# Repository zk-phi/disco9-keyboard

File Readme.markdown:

# よく光るマクロパッド

実験要素を多く含んだ９キーのマクロパッドです

- ２軸ジョイスティック (http://akizukidenshi.com/catalog/g/gP-04048/) を取り付けられます
- バックライト LED をスイッチとスイッチの間にもつけることができ、 LED 穴のついていないスイッチでも光らせられます
- (プレートがあれば ALPS スイッチも取り付けられます)

ジョイスティックは自由に値を取得して利用することができます。デフォルトのファームウェアにはカーソルを移動するサンプルが実装されています。

## パーツ

- 基板２枚 (片方は底板として利用)
- いつもの
  - ダイオード 1N4148w x9
  - 2 ピンタクトスイッチ x1
  - コンスルー付き ProMicro x1
- LED
  - SK6812mini 最大 x21
- ジョイスティック
  - JT8P-3.2T-B10K-1-16Y x1
- スイッチ
  - MX スイッチ x9
  - (プレートを用意すれば ALPS スイッチも可)
- ネジ類
  - M2 スペーサ 5mm 4 個
  - M2 ネジ 3~4mm 8 個
  - ゴム足 4 個

## 組み立て

- ダイオードを実装します
  - コの字の目印がカソード
  - ファームウェアを焼いたコンスルー付き ProMicro を差し込み、キースイッチのピンを接続する穴をピンセットなどでショートすることで動作確認できます

- LED を実装します
  - コの字の目印が Vcc
  - 穴に落とし込んで実装する普通のバックライトを、上段から下段に向かって図の順に
  - その後、表面に実装する怪しいバックライトを、今度は下段から上段に向かって図の順に
  - 途中まで実装した状態でも動作確認できます
    - ファームウェアを焼いたコンスルー付き ProMicro を差し込む
    - もし光らなければ、 RGB_TOG キーを (ピンセットなどでショートして) 押してみます
    - それでも光らない、あるいは不自然な点滅をしているなどの場合はハンダを付け直します

- タクトスイッチ、ジョイスティック、キースイッチをこの順に実装します
  - 背の低い部品からつけるのが楽です

- コンスルー付き Pro Micro を取り付けてファームウェアを焼きます
  - `zk-phi/qmk_firmware` にあります: `make handwired/disco9:default:avrdude`

- 底板をねじ止めしてゴム足を貼れば完成

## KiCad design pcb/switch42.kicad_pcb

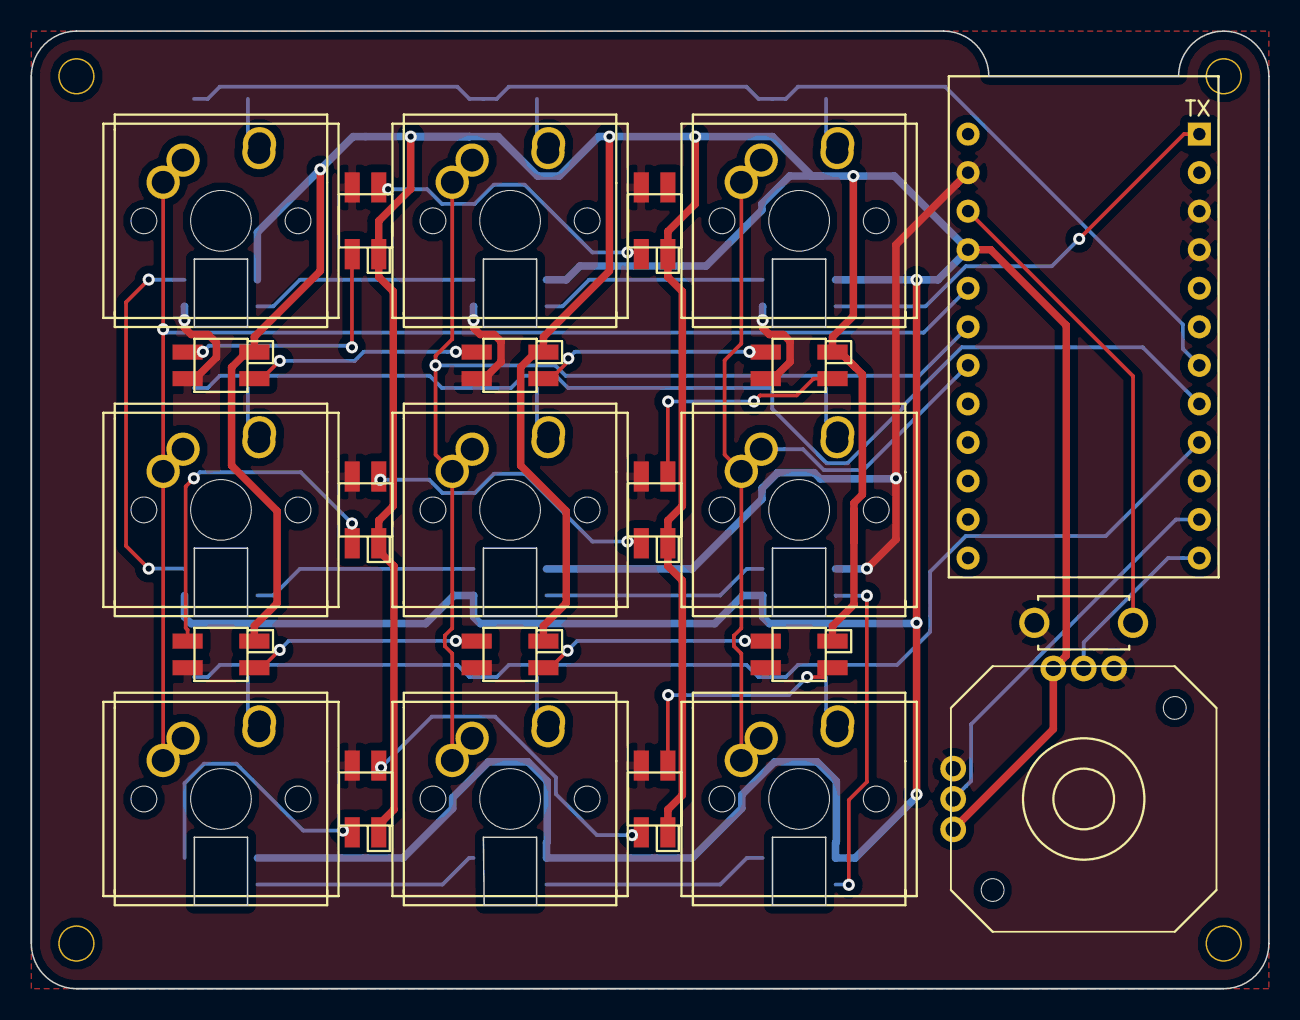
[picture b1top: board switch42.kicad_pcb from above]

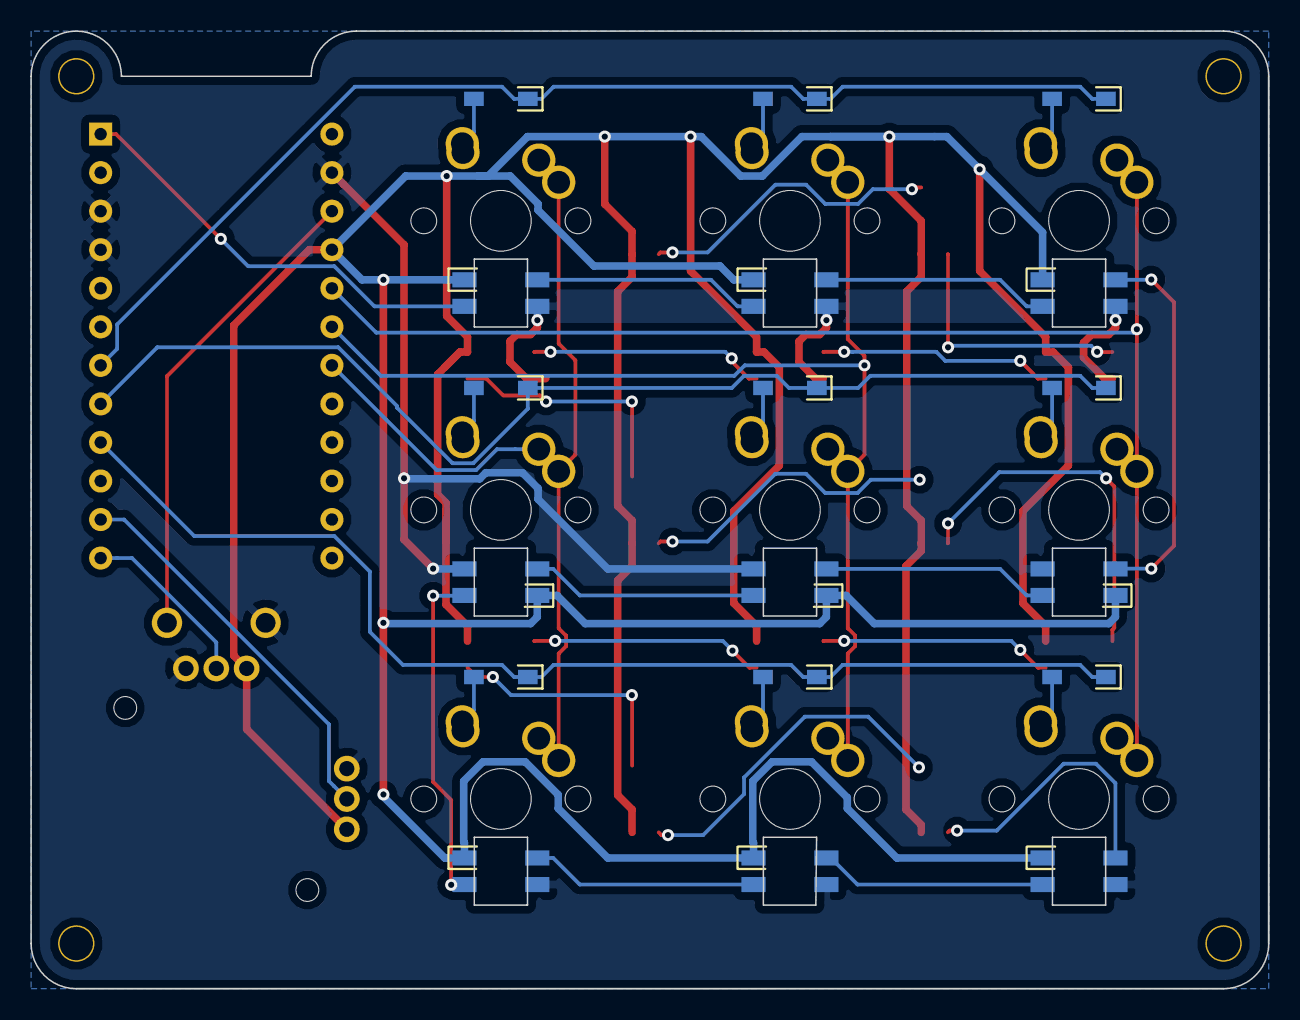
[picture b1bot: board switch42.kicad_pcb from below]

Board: 2 copper layers, 81.5 x 63.1 mm, 46 parts (9 on the bottom side), 41 nets.

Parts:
D1, D2, D3, D4, D5, D6, D7, D8, D9: D; D_SMD-irreversible
L1, L2, L3, L4, L5, L6, L7, L8, L9: SK6812MINI; SK6812MINI-irreversible
L10, L11, L12, L13, L14, L15, L21, L22, L23, L24, L25, L26: SK6812MINI; SK6812MINI-underglow-irreversible
Ref**: Val**; M2_SCREW_HOLE
Ref**#2, Ref**#3, Ref**#4: Val**; M2_SCREW_HOLE
SW1: SW_PUSH; ResetSW-irreversible
SW2, SW3, SW4, SW5, SW6, SW7, SW8, SW9, SW10: SW_PUSH; MX_or_ALPS-1.00u-irreversible
U1: ProMicro; ProMicro_Reversed_Conthrough-irreversible
U2: Val**; JT8P-3.2T

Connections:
GND: L1.2, L2.2, L3.2, L4.2, L5.2, L6.2, L7.2, L8.2, L9.2, L10.2, L11.2, L12.2, L13.2, L14.2, L15.2, L21.2, L22.2, L23.2, L24.2, L25.2, L26.2, SW1.2, U1.3, U1.4, U1.23, U2.1, U2.4
unnamed: D1.2, SW2.2
unnamed: D2.2, SW3.2
unnamed: D3.2, SW4.2
unnamed: D4.2, SW5.2
unnamed: D5.2, SW6.2
unnamed: D6.2, SW7.2
unnamed: D7.2, SW8.2
unnamed: D8.2, SW9.2
unnamed: D9.2, SW10.2
unnamed: L1.1, L4.3
unnamed: L2.1, L5.3
unnamed: L2.3, L7.1
unnamed: L3.1, L6.3
unnamed: L3.3, L8.1
unnamed: L4.1, L7.3
unnamed: L5.1, L8.3
unnamed: L6.1, L9.3
unnamed: L10.1, L11.3
unnamed: L10.3, L26.1
unnamed: L11.1, L12.3
unnamed: L12.1, L13.3
unnamed: L13.1, L14.3
unnamed: L14.1, L15.3
unnamed: L21.1, L22.3
unnamed: L22.1, L23.3
unnamed: L23.1, L24.3
unnamed: L24.1, L25.3
unnamed: L25.1, L26.3
VCC: L1.4, L2.4, L3.4, L4.4, L5.4, L6.4, L7.4, L8.4, L9.4, L10.4, L11.4, L12.4, L13.4, L14.4, L15.4, L21.4, L22.4, L23.4, L24.4, L25.4, L26.4, U1.21, U2.3, U2.6
Xin: U1.11, U2.5
Yin: U1.12, U2.2
col0: SW2.1, SW3.1, SW8.1, U1.20
col1: SW4.1, SW5.1, SW9.1, U1.19
col2: SW6.1, SW7.1, SW10.1, U1.18
led: L1.3, U1.1
reset: SW1.1, U1.22
row0: D1.1, D3.1, D5.1, U1.7
row1: D2.1, D4.1, D6.1, U1.8
row2: D7.1, D8.1, D9.1, U1.9
underglow: L9.1, L21.3

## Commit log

2020-06-11 Add experimental topplate with engrave
